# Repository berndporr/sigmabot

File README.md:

# sigmabot
Robot with linear servos and LIDAR

## Power supply

TODO. Needs to be fixed.

## LiDAR

RPLIDAR A1M8 is a 360degree omnidirectional laser scanner, based on the
triangulation ranging technique that emits modulated laser signal in
the near-infrared (NIR) light band (typ. 785nm) and this signal is
then reflected by a detected object.

In this project the UART communication interface was used to transmit
LiDAR data to the RaspberryPi rather than the alternatively provided
USB, due to the comparative simplicity of the communication protocol
and the transmitted data packets, which in turn ensures a quicker data
transmission.  The LiDAR’s motor is powered directly from the battery
(7.4V), while the scanning systems is powered by regulated 5V volts,
in order to meet the manufacturer’s requirements.

## Continuous Rotation Servo Motors

To make the robot movable, two Parallax continuous-rotation(CR) servo
motors were used. CR servos are modified servos that offer
open-loop speed control instead of the usual servos’ closed-loop
position control. This modification turns them into DC motors with
integrated motor driver, which in turn enables the bidirectional
rotation. Both the rotation speed and direction of the servo shaft of
each motor is controlled by a pulse width modulated (PWM) signal. Yet,
the lack of motor encoder or speed sensor to provide speed feedback
makes the CR servos prone to differences between desired and actual
speeds. Both motors have been powered
by a 5V regulated signal generated by the buck converter. The control
signals of the motors are 50Hz PWM signals, generated by two
RaspberryPi GPIO pins, where the higher the PWM duty cycle, the higher
the supplied powered to the motors and the faster the motor rotation
would be.  When tested, the motors exhibited non-linear response of
speed to applied PWM duty cycle. Second-order polynomial equation has
been therefore derived to describe their relationship.

```
Speed = −0.0773(PWM)^2 + 0.1787(PWM) − 0.0075
```

where PWM duty cycle ∈ [0, 1] (with 1 corresponding to 100% duty
cycle, resulting in maximum speed).

## Mechanical Design

The idea of the mechanical design was to make something simple and
easily and cheaply manufacturable.  It was decided to use the main PCB
not only for electrical connections but also as the chassis of the
robot.  With that in mind the PCB was laid out while keeping to the
similar dimensions of the Alphabot.

There are only few other mechanical parts required. Namely the wheels,
the ball castor, and some custom 3D-printed fittings. The chosen
wheels were Pololu 1090 Wheels with dimensions of 42x19mm. In order to
fit these wheels onto the servo motor shafts a custom wheel adaptor
was 3D-printed.

# Further docs

https://github.com/berndporr/sigmabot/blob/main/doc.pdf

# Credits
 - Ilina Todorova <2326960T@student.gla.ac.uk>
 - Bernd Porr <bernd.porr@glasgow.ac.uk>

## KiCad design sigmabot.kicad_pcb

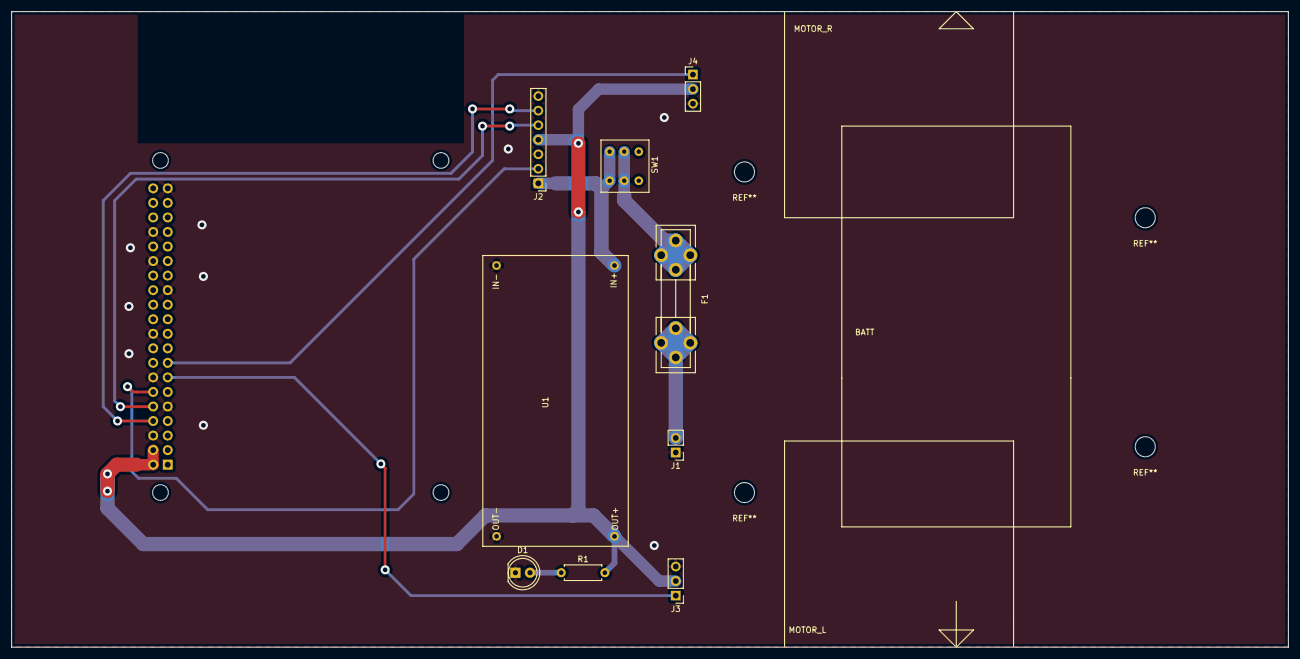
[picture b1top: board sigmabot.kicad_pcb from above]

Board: 2 copper layers, 223.0 x 111.0 mm, 10 parts (0 on the bottom side), 11 nets.

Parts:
D1: LED; LED_D5.0mm
F1: Fuse; Fuseholder5x20_horiz_open_universal_Type-III
J1: Conn_01x02; PinHeader_1x02_P2.54mm_Vertical
J2: Conn_01x07; PinHeader_1x07_P2.54mm_Vertical
J3: MOTOR_L; PinHeader_1x03_P2.54mm_Vertical
J4: MOTOR_R; PinHeader_1x03_P2.54mm_Vertical
R1: 510R; R_Axial_DIN0207_L6.3mm_D2.5mm_P7.62mm_Horizontal
RP1: Raspberry_Pi_2_3; raspberrypi_2_3
SW1: SW_DPDT_x2; sw_DPDT
U1: BUCK_CONV

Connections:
+5V: J2.4, J3.2, J4.2, R1.2, RP1.2, RP1.4, U1.3
+BATT: J2.1, SW1.1, SW1.4, U1.1
GND: D1.1, J1.1, J2.3, J2.7, J3.3, J4.3, RP1.6, RP1.9, RP1.14, RP1.20, RP1.25, RP1.30, RP1.34, RP1.39, U1.2, U1.4
LIDAR_RX: J2.6, RP1.8
LIDAR_TX: J2.5, RP1.10
MOTO_CTRL: J2.2, RP1.12
unnamed: D1.2, R1.1
unnamed: F1.1, SW1.2, SW1.5
unnamed: F1.2, J1.2
PWM_L: J3.1, RP1.13
PWM_R: J4.1, RP1.15

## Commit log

2022-05-19 Added kicad files
2022-05-19 Added credits
2022-05-19 Fixed e-mail
2022-06-21 Added docs
2022-06-21 Added link to doc
2022-06-21 needs to be a link
2022-06-21 A bit tidying up.
2022-07-07 Removed power supply stuff as it's not working.
2025-01-29 Just opened and closed it in newest kicad and it updated the PCB.
